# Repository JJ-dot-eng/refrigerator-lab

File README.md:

# Refrigerator Lab

업소용 냉장고를 브라우저에서 3D로 설계하고 살펴보는 웹앱입니다. 형태와 치수만 넣으면 부품 배치와 냉매 배관을 자동으로 만들고 간섭을 검사하며, 도면·부품 카탈로그·CAD 파일로 다듬을 수 있습니다. 실제 제품 재구성(HR24B, T-19-HC)과 냉동 사이클 시뮬레이션도 들어 있습니다.

**사이트:** https://jj-dot-eng.github.io/refrigerator-lab/

## 화면

| 경로 | 모델 | 내용 |
|---|---|---|
| `/` | **Hoshizaki HR24B** | 제조사 서비스 매뉴얼의 부품 배치와 냉매 회로 순서를 따른 3D 재구성. 밀폐형 압축기, 와이어-온-튜브 응축기, 드라이어, 모세관 코일, 핀-튜브 증발기, 둘레 액관까지 모든 배관을 연결했고, 운전 표시를 켜면 냉매 흐름과 증발기 팬이 움직입니다. |
| `/reference` | **True T-19-HC** | 제조사 사양서 치수로 만든 외형 모델과, 40개 운전점의 R290 냉동 사이클(P-h 선도), 24시간 냉각 실험. |
| `/models` | **사양서 기반 모델** | 냉장고 사양서(JSON)만으로 3D 모델과 냉매 배관을 자동 생성하고 검사한 결과. HR24B와 T-19-HC 두 형태를 같은 생성기로 만듭니다. |
| `/new` | **새로 만들기** | 형태(언더카운터·후면 응축기 / 리치인·하부 응축 유닛 / 리치인·상부 응축 유닛 / 리치인 2도어)를 고르고 외형 치수만 넣으면 부품 배치와 냉매 배관을 자동으로 만들고 검사합니다. 결과는 편집기로 넘겨 다듬을 수 있습니다. |
| `/editor` | **사양서 편집기** | 브라우저에서 사양서 값을 고치면 바로 3D를 다시 만들고 검사합니다. 도면(그림·PDF)을 배경에 깔고 부품을 도면 위치로 끌어 놓을 수도 있습니다. 압축기는 데이터시트 기반 카탈로그에서 고를 수 있고, STEP·IGES·STL·OBJ CAD 파일을 부품으로 가져와 배관을 연결할 수 있습니다. 작업은 브라우저에 자동 저장되고, JSON·OBJ 파일로 내려받을 수 있습니다. 서버로 보내는 데이터는 없습니다. |
| `/lab` | **MONO 120** | 120L 가상 설계. 가상 제어기, 문 개방·고장·정전 시험, 배선 하네스와 I/O 참조 기판. |

## 사용하기

설치할 필요 없이 **https://jj-dot-eng.github.io/refrigerator-lab/** 에 접속하면 됩니다. PC 브라우저(Chrome, Edge 등)를 권장합니다.

## 직접 실행 (개발용)

코드를 수정하거나 내 PC에서 돌리려면 Git과 Node.js 22.13 이상이 필요합니다.

```bash
git clone https://github.com/JJ-dot-eng/refrigerator-lab.git
cd refrigerator-lab/refrigerator
npm install
npm run dev
```

브라우저에서 http://localhost:3000 을 엽니다. Windows에서는 `npm install` 후 저장소 폴더의 `Start-MONO120.cmd`를 더블클릭해도 됩니다.

검사: `npm test`, `npm run lint`, `npx tsc --noEmit`, `npm run build`

## 구성

```
refrigerator/
├─ app/            화면 (hr24, new, models, editor, reference, lab)
├─ components/     3D 장면, 냉매 회로도
├─ generator/      사양서 → 3D 모델·배관 생성기와 자동 검사
├─ specs/          냉장고 사양서 (JSON) 와 양식 설명
├─ lib/            시뮬레이션 계산, CAD·저장소 보조 코드
├─ public/         3D 모델·배관·물성표 데이터와 생성 스크립트
└─ tests/          계산·모델 검증
.github/workflows/ GitHub Pages 자동 배포
```

모델별 근거, 가정, 한계, 데이터 재생성 방법은 [refrigerator/README.md](refrigerator/README.md)에 있습니다.

## 주의

- 3D 모델은 공개 도면과 일반 부품 치수를 바탕으로 한 **재구성**이며, 제조사 원본 CAD나 실측값이 아닙니다.
- 시뮬레이션 결과는 가정 모델에서 나온 값이며, 제품 성능이나 에너지 등급이 아닙니다.
- 제조사 매뉴얼과 사양서는 저작권 때문에 저장소에 포함하지 않았습니다. 화면에서는 제조사 원본 링크를 안내합니다.
- Hoshizaki, True는 각 회사의 상표이며, 이 프로젝트는 해당 회사와 관련이 없습니다.

## 라이선스

[MIT](LICENSE). 제조사 문서와 상표에는 적용되지 않습니다. 함께 쓰는 라이브러리 중 occt-import-js(OpenCascade)는 LGPL-2.1, pdf.js는 Apache-2.0입니다.

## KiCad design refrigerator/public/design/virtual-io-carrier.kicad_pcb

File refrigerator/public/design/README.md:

# 1도어 냉장고 시뮬레이션용 설계 자료

이 자료는 가상 운전 시뮬레이터의 설계 입력이다. 압축기 또는 실제 제품의 측정 성능표가 아니다.

## 냉동 사이클

CoolProp 8.0.0으로 R600a 정상상태 증기압축 사이클을 실제 계산했다. 증발온도 -25..0 °C, 응축온도 30..65 °C, 각각 5 K 간격의 48개 점이다. 과열 5 K, 과냉 3 K, 등엔트로피 효율 0.60, 모터 효율 0.85, 질량유량 0.00045 kg/s를 가정했다. 앱 기준점은 증발 -15 °C / 응축 40 °C다.

압축기 입구 h1은 과열 증기, h2는 효율을 반영한 토출, h3은 과냉 액, h4=h3은 등엔탈피 팽창이다. 냉각량은 m(h1-h4), 축동력은 m(h2-h1), 전력은 축동력/0.85다. 냉매 응축 방열량 m(h2-h3)에 별도의 모터 손실을 더해야 총 외부 방열량이 된다. 모든 점에서 냉매 측 에너지수지 오차가 1e-8 W 미만임을 확인했다.

`cycle-table.json`은 앱 보간용이고 `r600a-cycle-grid.json`은 상세 SI 값이다. 모델에는 압축기 맵, 충전량, 압력손실, 냉매 과도 분포, 착상·제상 해석이 포함되지 않는다. 고정 질량유량은 설계 가정이며 실제 특정 압축기와의 일치를 뜻하지 않는다.

## 기구

CadQuery가 `one-door-120l.step` 및 `one-door-120l.stl`을 생성한다. 캐비닛과 문 외형은 550 × 580 × 1000 mm, 최소 측벽 단열은 50 mm, 문 두께는 60 mm다. 후면 응축기 개념 형상은 17.5 mm 추가 돌출한다. 내함 유효 공간 가정 137.7 L에서 하단 기계실 돌출 17.82 L를 빼면 119.88 L, 선반 3개의 재료 부피를 빼면 117.71 L다. 작은 피팅과 증발기도 공간을 차지하며 공인 수납용량 시험치는 아니다.

STEP은 부품 위치·외피를 표현한 개념 조립체다. 기계실 돌출 형상은 내부 금지영역을 표시하는 솔리드라 압축기와 겹친다. 제조용 케이스 벽·배관·기밀 구조·체결부 완성 모델로 해석하면 안 된다.

현재 설치된 CadQuery Python 환경은 `import cadquery`만 실행해도 정상 출력 후 종료 시 Windows 오류 -1073740940(힙 손상)을 반환한다. 모델 파일 생성과 에너지수지 assertion은 완료됐으며, 모델 파일 검증은 독립 FreeCAD 로더로 수행한다. 이는 생성 코드의 계산 오류와 구분되는 설치 환경 문제이며 종료 성공으로 숨기지 않았다.

## 배선과 PCB

WireViz YAML에서 실제 HTML/SVG/PNG 연결도를 생성했다. 핀 정의는 `design-metadata.json`에 있다. 인버터는 가상 UART 명령 장치이며 3.3 V 참조 전압, GND, TX/RX, ENABLE만 표현한다. 전력 인버터 회로는 없다. 전선 길이는 배치에 따른 예시 가정으로 3D 경로에서 자동 산출한 값은 아니다.

`virtual-io-carrier.kicad_pcb`는 95 × 60 mm의 실제 KiCad 연결 기판 파일이다. J0 가상 제어기 포트와 J1..J6 커넥터 사이의 배선을 담는다. MCU, 전압조정기, NTC 분압 저항, EEPROM IC, 전력소자 등은 실장하지 않은 I/O 연결 참조다. 따라서 완성된 냉장고 메인 PCB로 표기하지 않는다. 라이브러리와 DRC 보고서를 동봉한다.

## 근거

- [CoolProp R600a 물성](https://coolprop.org/fluid_properties/fluids/IsoButane.html)
- [CoolProp SI API](https://coolprop.org/coolprop/HighLevelAPI.html)
- [CadQuery 형상 내보내기](https://cadquery.readthedocs.io/en/latest/importexport.html)
- [WireViz](https://github.com/wireviz/WireViz)

생성 스크립트는 동일 폴더 안에 있으며, 제품 성능 가정과 라이브러리 기반 물성 계산을 구분해 재생성할 수 있다.

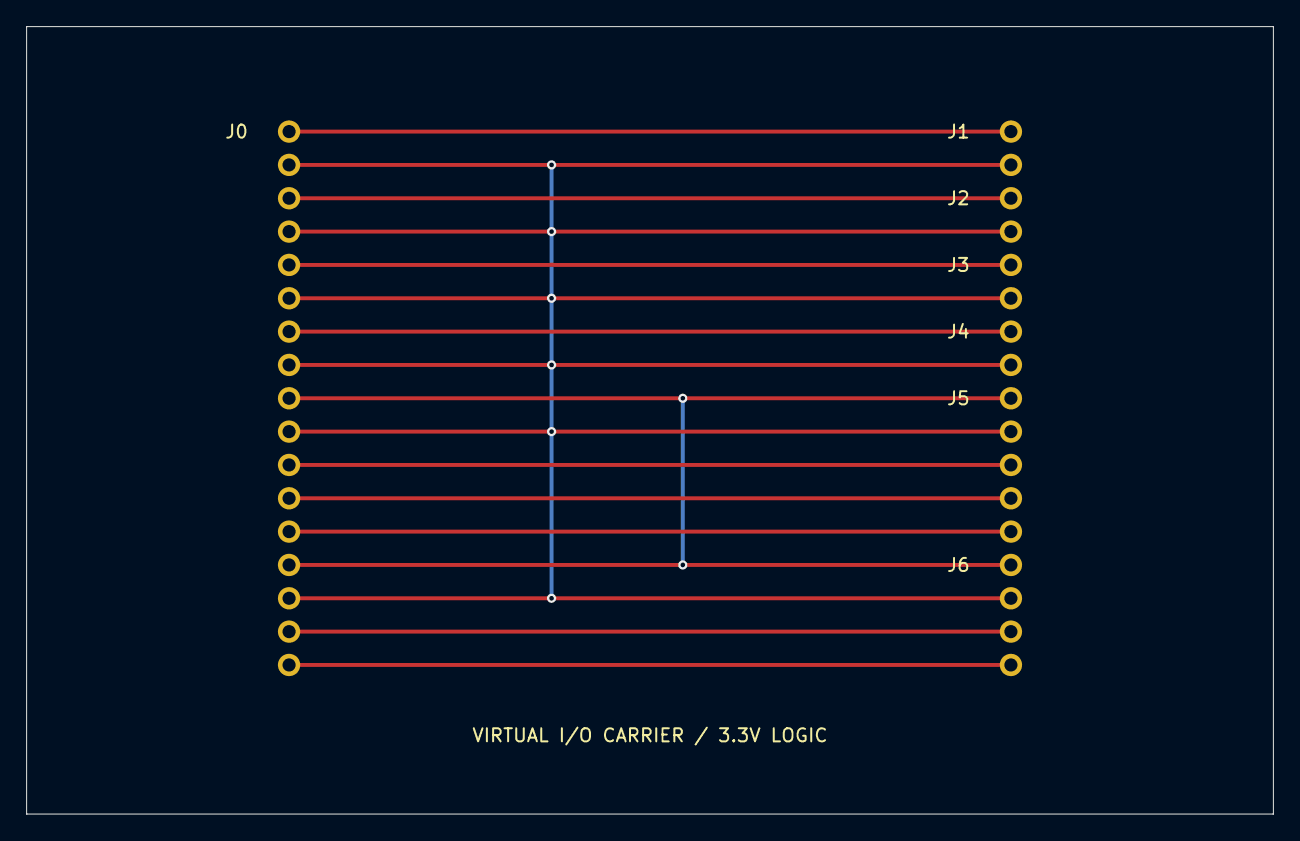
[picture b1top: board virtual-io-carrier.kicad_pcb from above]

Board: 2 copper layers, 95.0 x 60.0 mm, 7 parts (0 on the bottom side), 11 nets.

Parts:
J0: VIRTUAL MCU I/O CARRIER; J0
J1: SIMULATION INTERFACE; J1
J2: SIMULATION INTERFACE; J2
J3: SIMULATION INTERFACE; J3
J4: SIMULATION INTERFACE; J4
J5: SIMULATION INTERFACE; J5
J6: SIMULATION INTERFACE; J6

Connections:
3V3: J0.9, J0.14, J5.1, J6.1
5V: J0.1, J1.1
ADC_CABINET: J0.3, J2.1
ADC_EVAP: J0.5, J3.1
DOOR_GPIO_PULLUP: J0.7, J4.1
ENABLE: J0.13, J5.5
GND: J0.2, J0.4, J0.6, J0.8, J0.10, J0.15, J1.2, J2.2, J3.2, J4.2, J5.2, J6.2
SCL: J0.16, J6.3
SDA: J0.17, J6.4
UART_RX: J0.12, J5.4
UART_TX: J0.11, J5.3

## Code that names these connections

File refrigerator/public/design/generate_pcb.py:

from pathlib import Path
import pcbnew as p
OUT=Path(__file__).parent
libdir=OUT/'ReferenceHeaders.pretty'
libdir.mkdir(exist_ok=True)
(OUT/'fp-lib-table').write_text('(fp_lib_table (lib (name "ReferenceHeaders") (type "KiCad") (uri "${KIPRJMOD}/ReferenceHeaders.pretty") (options "") (descr "Generated through-hole reference headers")))',encoding='utf-8')
b=p.BOARD()
def pt(x,y): return p.VECTOR2I(p.FromMM(x),p.FromMM(y))
def segment(x1,y1,x2,y2,layer,net=None):
 if net is None:
  s=p.PCB_SHAPE();s.SetShape(p.SHAPE_T_SEGMENT);s.SetWidth(p.FromMM(.05))
 else:
  s=p.PCB_TRACK(b);s.SetWidth(p.FromMM(.3));s.SetNetCode(net.GetNetCode())
 s.SetStart(pt(x1,y1));s.SetEnd(pt(x2,y2));s.SetLayer(layer);b.Add(s)
for a,c in [((0,0),(95,0)),((95,0),(95,60)),((95,60),(0,60)),((0,60),(0,0))]:segment(*a,*c,p.Edge_Cuts)
pins=[('J1',['5V','GND']),('J2',['ADC_CABINET','GND']),('J3',['ADC_EVAP','GND']),('J4',['DOOR_GPIO_PULLUP','GND']),('J5',['3V3','GND','UART_TX','UART_RX','ENABLE']),('J6',['3V3','GND','SCL','SDA'])]
names=[n for _,ns in pins for n in ns]
nets={}
for n in set(names):
 net=p.NETINFO_ITEM(b,n);b.Add(net);nets[n]=net
def header(ref,value,x,y,signals):
 f=p.FOOTPRINT(b);f.SetReference(ref);f.SetValue(value);f.SetPosition(pt(x,y));f.SetFPID(p.LIB_ID('ReferenceHeaders',ref))
 f.Reference().SetPosition(pt(x-4,y));f.Reference().SetTextSize(pt(1,1));f.Reference().SetLayer(p.F_SilkS)
 f.Value().SetVisible(False)
 for i,n in enumerate(signals):
  pad=p.PAD(f);pad.SetNumber(str(i+1));pad.SetAttribute(p.PAD_ATTRIB_PTH);pad.SetShape(p.PAD_SHAPE_CIRCLE)
  pad.SetSize(pt(1.7,1.7));pad.SetDrillSize(pt(1,1));pad.SetLayerSet(p.PAD.PTHMask());pad.SetPosition(pt(x,y+i*2.54));pad.SetNet(nets[n]);f.Add(pad)
 b.Add(f)
 p.PCB_IO_MGR.FindPlugin(p.PCB_IO_MGR.KICAD_SEXP).FootprintSave(str(libdir.resolve()),f)
header('J0','VIRTUAL MCU I/O CARRIER',20,8,names)
i=0
for ref,ns in pins:
 header(ref,'SIMULATION INTERFACE',75,8+i*2.54,ns)
 for n in ns:
  y=8+i*2.54
  segment(20,y,75,y,p.F_Cu,nets[n])
  if n in ['GND','3V3']:
   x=40 if n=='GND' else 50
   via=p.PCB_VIA(b);via.SetPosition(pt(x,y));via.SetWidth(p.FromMM(.7));via.SetDrill(p.FromMM(.35));via.SetViaType(p.VIATYPE_THROUGH);via.SetLayerPair(p.F_Cu,p.B_Cu);via.SetNetCode(nets[n].GetNetCode());b.Add(via)
  i+=1
for n,x in [('GND',40),('3V3',50)]:
 ys=[8+i*2.54 for i,a in enumerate(names) if a==n]
 segment(x,min(ys),x,max(ys),p.B_Cu,nets[n])
t=p.PCB_TEXT(b);t.SetText('VIRTUAL I/O CARRIER / 3.3V LOGIC');t.SetPosition(pt(47.5,54));t.SetTextSize(pt(1,1));t.SetLayer(p.F_SilkS);b.Add(t)
p.SaveBoard(str(OUT/'virtual-io-carrier.kicad_pcb'),b)
print('Saved real KiCad board: 95 x 60 mm, 7 connectors, 17 I/O positions. Carrier only; no MCU/power/inverter circuitry.')
